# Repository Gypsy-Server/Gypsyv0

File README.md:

*A local file viewer built on the ESP8266*

---

## What is here

- **Local file browsing** over Wi-Fi  
- **SD card (FAT32/MBR)** storage support   
- Runs standalone — powered via USB or external 5 V  or 3.3V

---

## Hardware

- **MCU:** ESP8266(12E)
- **Storage:** SD card(SPI MODE)  
- **Voltage Regulator AMS117 3.3V**
- **Ch340C USB TO TTL Converter chip**
- **Passive Components:** Resistor ,Capacitor

You can view the full schematic and PCB in the `usb_stick_kicadfiles/` folder (KiCad project).

---

##  What to do 

1. Flash gypsy.ino using Arduino IDE or PlatformIO.  
2. Open Serial Monitor to get the IP (eg 192.168.x.x)
3. Open in any browser on Computer or any device connected to that Network

---
## What you will see

Home Page

File viewing 

 Contents

 Mp4 full screen view

## What i have seen SO FAR
- file uploading speed is Limited (average 150-250KB/s)
- Slower playing Larger files (greater than 50MB)
- but Good in MP3 handling , doesn't stuck (80KB of RAM is sufficient in ths case)
- Sometimes SD card initialization fails (random)

## Some Fatal Issues 
- **The original PCB has fatal a flaw, SD card Chip detect Pin as CS PIN , so don't use this project as it is , Also the Driver chip of sd card is 
not necessary so for better design remove it esp8266 can drive sd card itself by 3.3v logic, for my case i have used and extra thin wire
to cover up my mistake**
so i would recommend to use this project [Hackstar-io](https://www.hackster.io/Neutrino-1/wireless-sd-card-reader-esp8266-de7f07)
for the Hardware Layout

**Mistakes**

##  What I’m Exploring Next

- Network sharing (I have tested it with Ngrok proxy tunneling to my friends , but if multiple people use at same time then it stops)  
- ESP32 port for faster WIFI throughput  
- Power optimization and case design( even smaller any small processor like Raspberry Pi Zero or ESP32 higher variant)
- Larger Video playback(cinema of Some Sort)

---

##  Feedback Wanted

This is still a **work in progress**, and I’d love your thoughts on:

- Firmware structure and web interface flow  
- PCB layout or power-handling tips  
- Ideas for extending it into a full mini NAS

If you’ve built anything similar — or see a way to make this smarter, faster, or cleaner — I’m all ears.

---

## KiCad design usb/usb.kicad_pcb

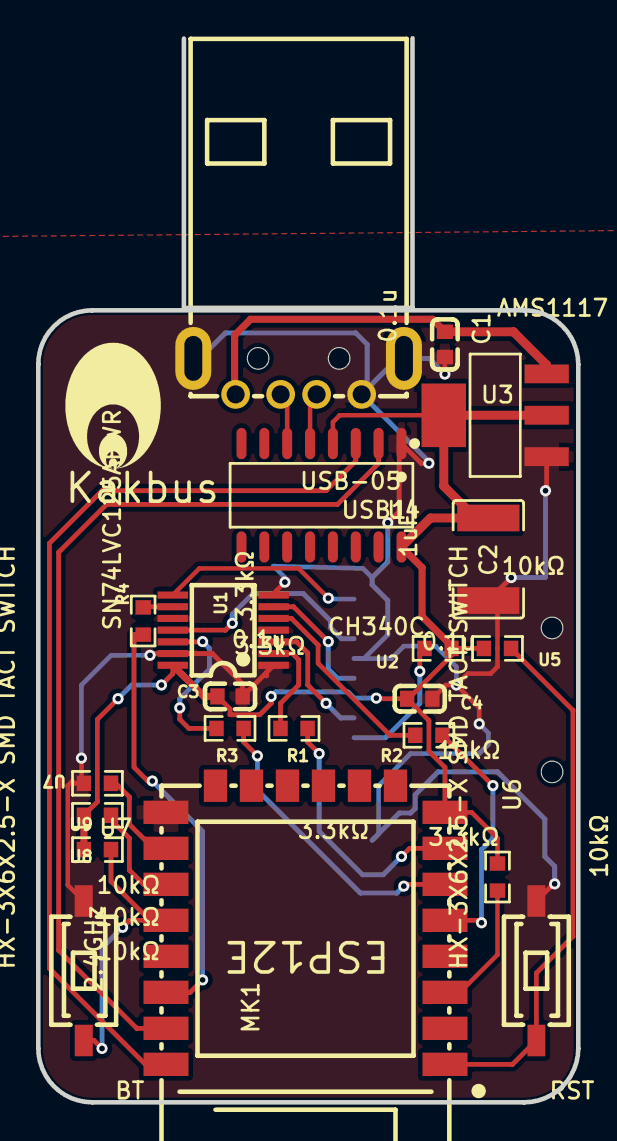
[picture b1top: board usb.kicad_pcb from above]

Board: 2 copper layers, 30.0 x 59.1 mm, 22 parts (1 on the bottom side), 25 nets.

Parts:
BT: HX-3X6X2.5-X SMD TACT SWITCH; SW-SMD_HX-3X6X2.5-X
C1, C3, C4: 0.1u; C0603
C2: 1uF; C1812
CARD1: TF PUSH; TF-SMD_TF-PUSH
MK1: 2.4GHz; WIFIM-SMD_ESP-12E-BR
R1, R2, R3, R4: 3.3kΩ; R0603
RST: HX-3X6X2.5-X SMD TACT SWITCH; SW-SMD_HX-3X6X2.5-X
U1: SN74LVC125APWR; TSSOP-14_L5.0-W4.4-P0.65-LS6.4-BL
U2, U5, U6, U7, U8, U9: 10kΩ; R0603
U3: AMS1117; SOT-223_L6.5-W3.5-P2.30-LS7.0-BR
U4: CH340C; SOP-16_L10.0-W3.9-P1.27-LS6.0-BL
USB1: USB-05; USB-A-TH_USB-05

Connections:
3.3V: C2.2, C3.1, C4.1, CARD1.4, MK1.8, U1.14, U2.1, U3.2, U3.4, U4.4, U4.16, U5.1, U6.1, U8.2, U9.2
BT: BT.1, MK1.18, U8.1
CARD1_2: CARD1.2, U2.2
CS: MK1.20, R4.2
CSH: CARD1.CD, U1.8
DIH: CARD1.3, U1.3
DOH: CARD1.7, U1.11
GND: BT.2, C1.1, C2.1, C3.2, C4.2, CARD1.6, CARD1.10, CARD1.11, CARD1.12, CARD1.13, MK1.15, RST.2, U1.1, U1.4, U1.7, U1.10, U1.13, U3.1, U4.1, U7.2, USB1.4, USB1.5, USB1.6
MISO: MK1.6, R3.2
MK1_3: MK1.3, U6.2
MK1_16: MK1.16, U7.1
MK1_17: MK1.17, U9.1
MOSI: MK1.7, R1.1
RST: MK1.1, RST.1, U5.2
RXD: MK1.22, U4.3
SCK: MK1.5, R2.1
SCKH: CARD1.5, U1.6
TXD: MK1.21, U4.2
U1_2: R1.2, U1.2
U1_5: R2.2, U1.5
U1_9: R4.1, U1.9
U1_12: R3.1, U1.12
U4_5: U4.5, USB1.3
U4_6: U4.6, USB1.2
VCC: C1.2, U3.3, USB1.1

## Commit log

2025-11-02 added gypsy.ino
2025-11-02 added README.md
2025-11-02 change gypsy.ino
2025-11-02 added images README.md
2025-11-02 changed README.md
2025-11-02 chagned README.md
2025-11-02 kicad
2025-11-02 kicad files , have a fatal error , i have put chip detect pin as CS haha
2025-11-03 removed old files
2025-11-03 changed README
2025-11-03 changed src
